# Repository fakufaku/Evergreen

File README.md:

Evergreen
=========

A blinky replacement for homemade cookies. This funky sparkly christmas tree features a completely reprogramable ATtiny85.
Also, large pads allow to strap it to some other contraption. The imagination is the limit!

Bill of Material
----------------

* ATtiny85 (SOIC8),
* 5x SMD LED (0805),
* 5x corresponding resistors (0805),
* 1x tiny [slide switch](http://www.mouser.com/Search/ProductDetail.aspx?R=SSAJ120100virtualkey68800000virtualkey688-SSAJ120100),
* and a CR 2032 coin cell holder such as [this one](http://www.mouser.com/Search/ProductDetail.aspx?R=3034virtualkey53400000virtualkey534-3034).

Voltage considerations
----------------------

The board runs directly from the battery voltage (3V or less), so the LED voltage drop should be 2.5V or less.

Printing and cutting
--------------------

Mask files are provided to print eight boards at a time. Alignment points are also provided. After printing the mask, the printed side (with the ink) should go
directly against the copper (hence the top mask is mirrored).

The alignment marks on the cut outline correspond to the alignment mark of the mask. This is to allow CNC cutting of the boards.

To print less boards, it is enough to delete the extra boards in the files.

License
-------

Beerware ;)

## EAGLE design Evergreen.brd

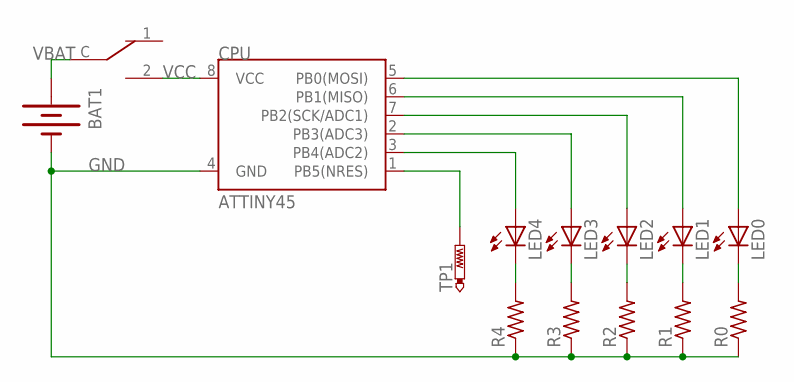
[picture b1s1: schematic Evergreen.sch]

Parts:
BAT1: BATTERY20SMD; BATTCON_20MM
CPU: ATTINY45; SO08-EIAJ
LED0, LED1, LED2, LED3, LED4: LEDCHIP-LED0805; CHIP-LED0805
R0, R1, R2, R3, R4: R-US_M0805; M0805
SWITCH: SWITCH-SPDT; SSAJ120100
TP1: PTR1B2,54; B2,54

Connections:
GND: BAT1.2 (-), CPU.4 (GND), R0.1, R1.1, R2.1, R3.1, R4.1
unnamed: LED4.C, R4.2
unnamed: LED3.C, R3.2
unnamed: LED2.C, R2.2
unnamed: LED1.C, R1.2
unnamed: LED0.C, R0.2
PB0: CPU.5 (PB0(MOSI)), LED0.A
PB1: CPU.6 (PB1(MISO)), LED1.A
PB2: CPU.7 (PB2(SCK/ADC1)), LED2.A
PB3: CPU.2 (PB3(ADC3)), LED3.A
PB4: CPU.3 (PB4(ADC2)), LED4.A
PB5: CPU.1 (PB5(NRES)), TP1.TP
VBAT: BAT1.1 (+), BAT1.3 (+), SWITCH.C
VCC: CPU.8 (VCC), SWITCH.2

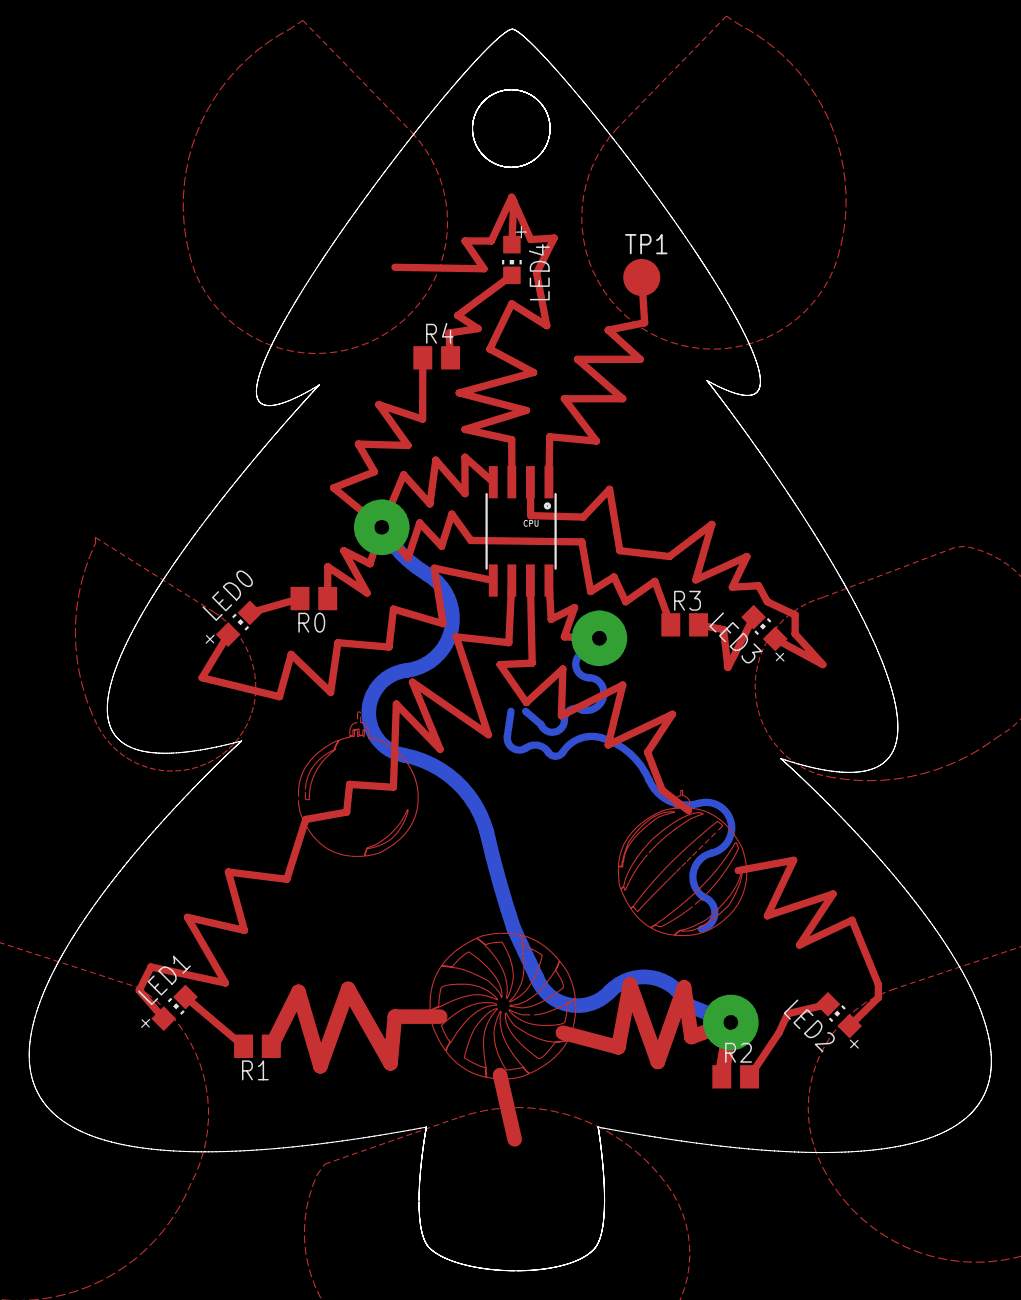
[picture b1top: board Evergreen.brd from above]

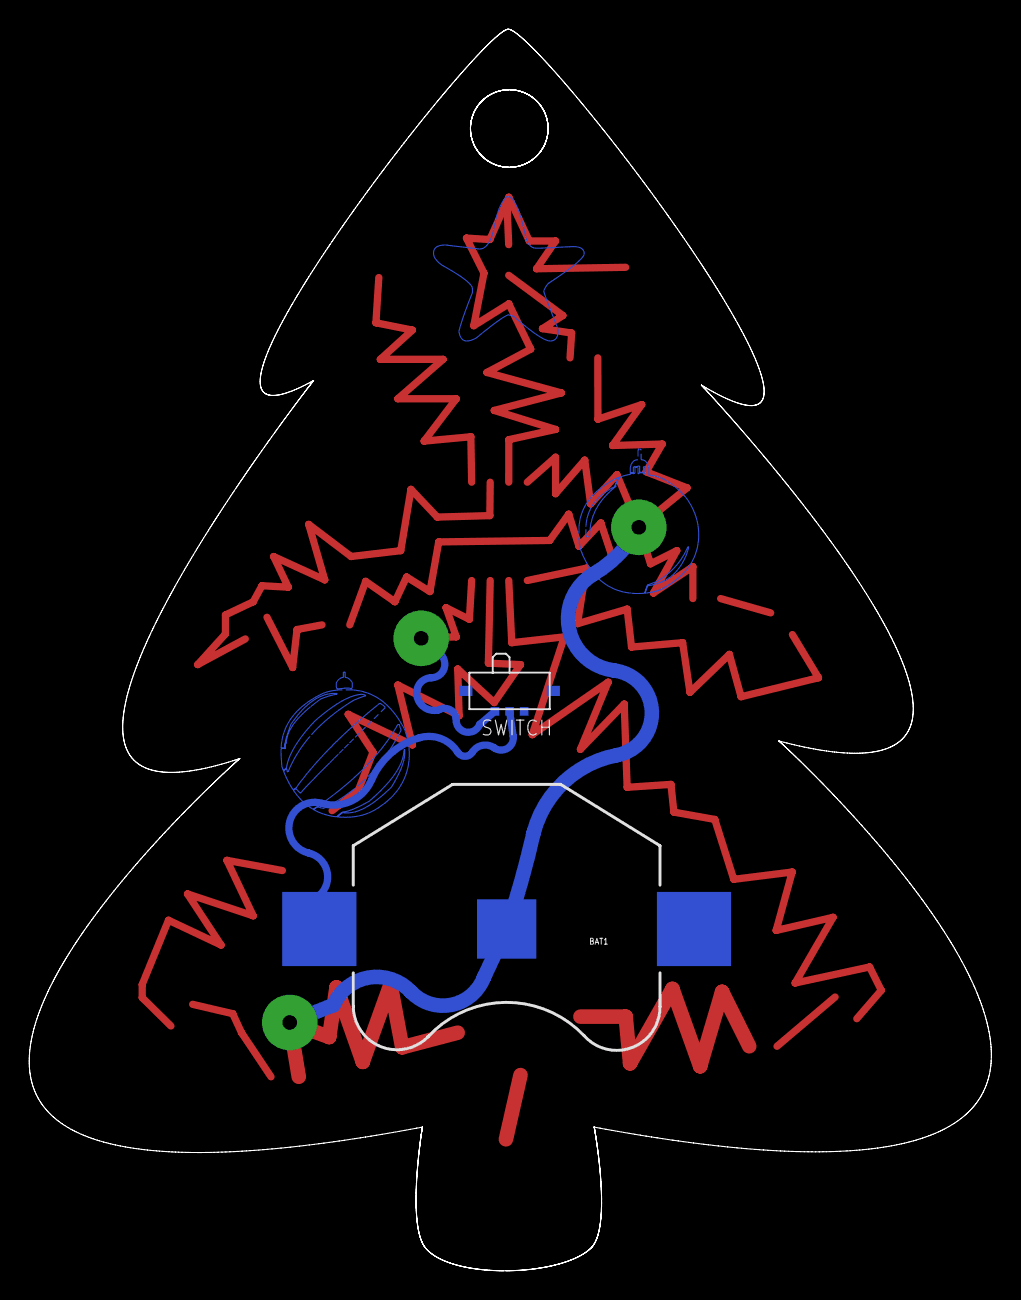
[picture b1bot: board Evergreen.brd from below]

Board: 2 copper layers, 65.9 x 85.0 mm, 16 parts (2 on the bottom side), 14 nets.

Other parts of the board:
U$1, U$2: ALIGN

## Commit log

2013-12-25 First commit.
2013-12-25 README
2013-12-25 typo
